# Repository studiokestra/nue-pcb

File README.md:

# Nue PCB rev1.1

This is the open source PCB for the Nue keyboard. It's minimally designed (as intentioned) with ISO support and basic 60% layout options. The Nue PCB has gasket mounting tabs and as such will not work on any other keyboard. Fuse / ESD protection was not implemented initially as this was taken care of by the unifed C3 daughterboard, however future revisions will have it onboard as backup. These files are provided as-is and are intended for tinkerers, do not expect warranty or support to be provided.

## Features
- Designed with KiCad 6.0+
- Compatible with QMK/VIA
- Only works with Nue PCB
- Utilizes Unified C3 daughterboard or compatible equivalents
- ISP header

## Supported layouts

## Ordering
The files necessary to produce the PCBs via JLCPCB are located in the production folder.

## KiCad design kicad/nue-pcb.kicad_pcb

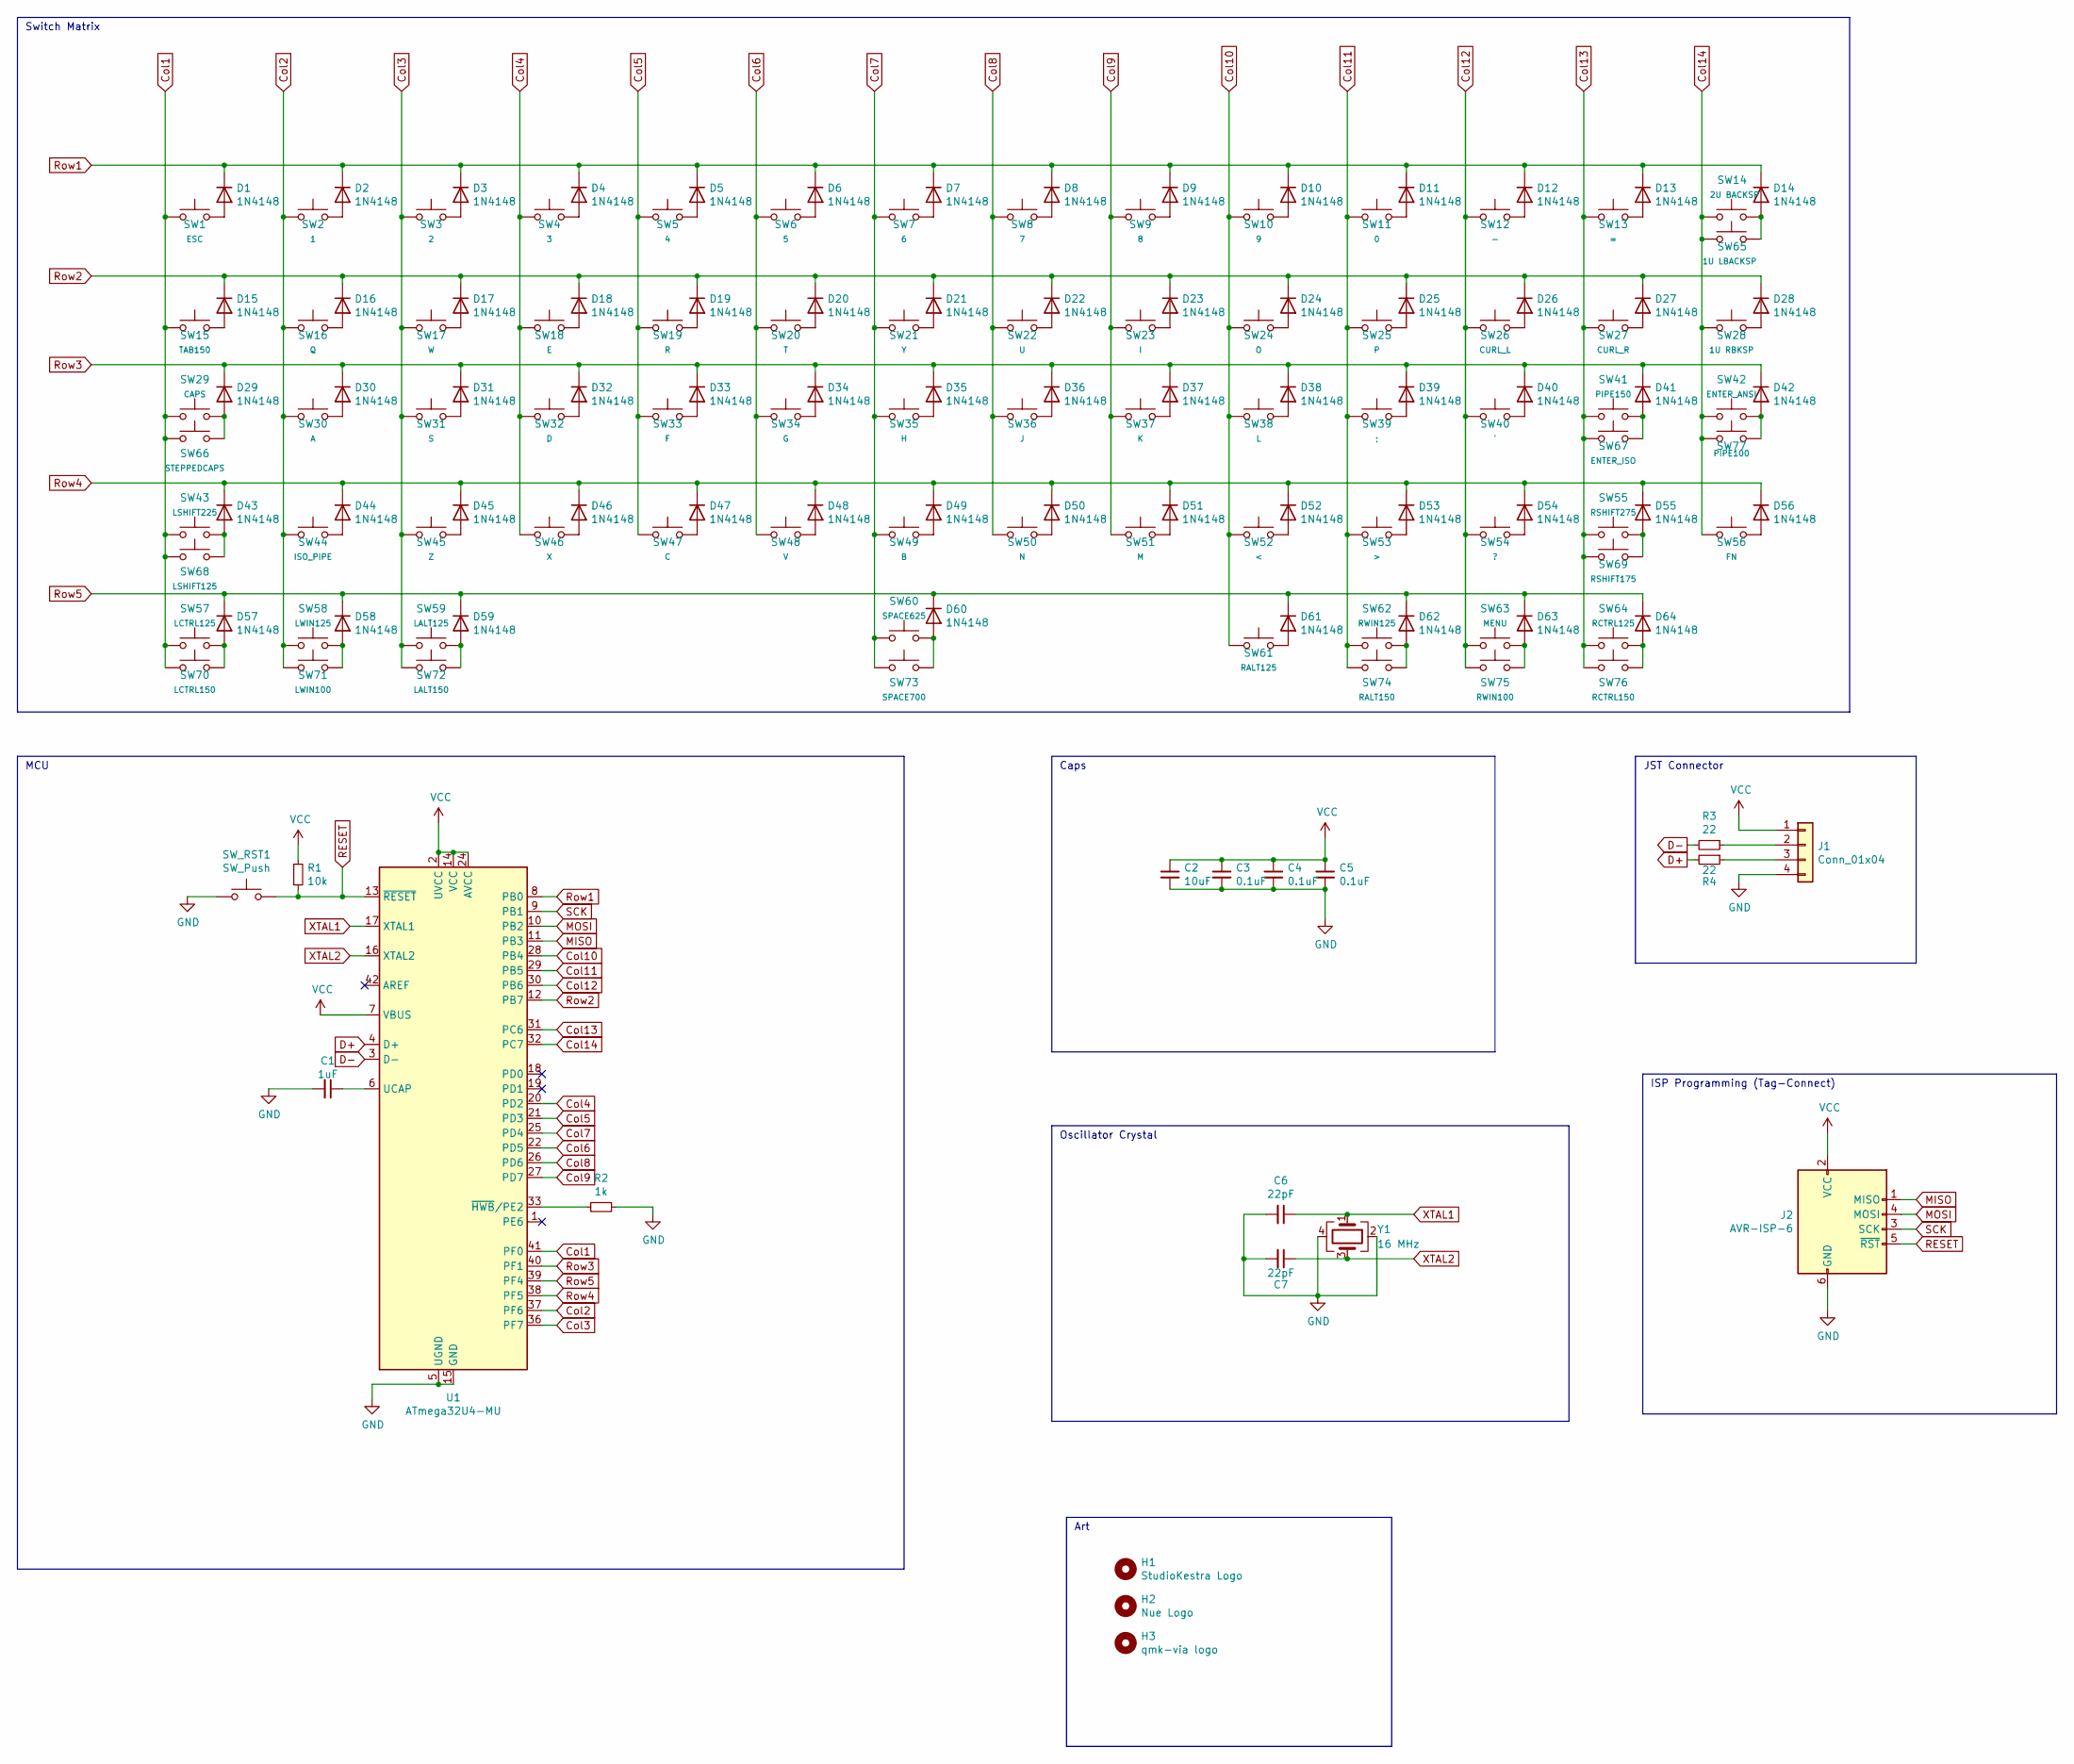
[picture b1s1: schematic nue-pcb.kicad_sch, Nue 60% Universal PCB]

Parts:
C1: 1uF; C_0603_1608Metric
C2: 10uF; C_0603_1608Metric
C3, C4, C5: 0.1uF; C_0603_1608Metric
C6, C7: 22pF; C_0603_1608Metric
D1, D2, D3, D4, D5, D6, D7, D8, D9, D10, D11, D12, D13, D14, D15, D16, D17, D18, D19, D20, D21, D22, D23, D24, D25, D26, D27, D28, D29, D30, D31, D32, D33, D34, D35, D36, D37, D38, D39, D40, D41, D42, D43, D44, D45, D46, D47, D48, D49, D50, D51, D52, D53, D54, D55, D56, D57, D58, D59, D60, D61, D62, D63, D64: 1N4148; D_SOD-123
H1: StudioKestra Logo; sk-square-mask-md
H2: Nue Logo; nue-logo
H3: qmk-via logo; qmk-via
J1: Conn_01x04; JST_BM04B-ASRS
J2: AVR-ISP-6; Conn_AVR_ISP_6
R1: 10k; R_0603_1608Metric
R2: 1k; R_0603_1608Metric
R3, R4: 22; R_0603_1608Metric
SW1: ESC; MX100
SW2: 1; MX100
SW3: 2; MX100
SW4: 3; MX100
SW5: 4; MX100
SW6: 5; MX100
SW7: 6; MX100
SW8: 7; MX100
SW9: 8; MX100
SW10: 9; MX100
SW11: 0; MX100
SW12: -; MX100
SW13: =; MX100
SW14: 2U BACKSP; MX200
SW15: TAB150; MX150
SW16: Q; MX100
SW17: W; MX100
SW18: E; MX100
SW19: R; MX100
SW20: T; MX100
SW21: Y; MX100
SW22: U; MX100
SW23: I; MX100
SW24: O; MX100
SW25: P; MX100
SW26: CURL_L; MX100
SW27: CURL_R; MX100
SW28: 1U RBKSP; MX100
SW29: CAPS; MX175
SW30: A; MX100
SW31: S; MX100
SW32: D; MX100
SW33: F; MX100
SW34: G; MX100
SW35: H; MX100
SW36: J; MX100
SW37: K; MX100
SW38: L; MX100
SW39: ;; MX100
SW40: '; MX100
SW41: PIPE150; MX150
SW42: ENTER_ANSI; MX225R
SW43: LSHIFT225; MX225
SW44: ISO_PIPE; MX100
SW45: Z; MX100
SW46: X; MX100
SW47: C; MX100
SW48: V; MX100
SW49: B; MX100
SW50: N; MX100
SW51: M; MX100
SW52: <; MX100
SW53: >; MX100
SW54: ?; MX100
SW55: RSHIFT275; MX275
SW56: FN; MX100
SW57: LCTRL125; MX125
SW58: LWIN125; MX125
SW59: LALT125; MX125
SW60: SPACE625; MX625R
SW61: RALT125; MX125
SW62: RWIN125; MX125
SW63: MENU; MX125
SW64: RCTRL125; MX125
SW65: 1U LBACKSP; MX100
SW66: STEPPEDCAPS; MX125
SW67: ENTER_ISO; MXISOEnter
SW68: LSHIFT125; MX125
SW69: RSHIFT175; MX175
SW70: LCTRL150; MX150
SW71: LWIN100; MX100
SW72: LALT150; MX150
SW73: SPACE700; MX700R
SW74: RALT150; MX150
SW75: RWIN100; MX100
SW76: RCTRL150; MX150
SW77: PIPE100; MX100
SW_RST1: SW_Push; pushbtn_C319436
U1: ATmega32U4-MU; QFN-44-1EP_7x7mm_P0.5mm_EP5.2x5.2mm
Y1: 16 MHz; Crystal_SMD_2520-4Pin_2.5x2.0mm

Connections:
Col1: SW1.1, SW15.1, SW29.1, SW43.1, SW57.1, SW66.1, SW68.1, SW70.1, U1.41 (PF0)
Col2: SW2.1, SW16.1, SW30.1, SW44.1, SW58.1, SW71.1, U1.37 (PF6)
Col3: SW3.1, SW17.1, SW31.1, SW45.1, SW59.1, SW72.1, U1.36 (PF7)
Col4: SW4.1, SW18.1, SW32.1, SW46.1, U1.20 (PD2)
Col5: SW5.1, SW19.1, SW33.1, SW47.1, U1.21 (PD3)
Col6: SW6.1, SW20.1, SW34.1, SW48.1, U1.22 (PD5)
Col7: SW7.1, SW21.1, SW35.1, SW49.1, SW60.1, SW73.1, U1.25 (PD4)
Col8: SW8.1, SW22.1, SW36.1, SW50.1, U1.26 (PD6)
Col9: SW9.1, SW23.1, SW37.1, SW51.1, U1.27 (PD7)
Col10: SW10.1, SW24.1, SW38.1, SW52.1, SW61.1, U1.28 (PB4)
Col11: SW11.1, SW25.1, SW39.1, SW53.1, SW62.1, SW74.1, U1.29 (PB5)
Col12: SW12.1, SW26.1, SW40.1, SW54.1, SW63.1, SW75.1, U1.30 (PB6)
Col13: SW13.1, SW27.1, SW41.1, SW55.1, SW64.1, SW67.1, SW69.1, SW76.1, U1.31 (PC6)
Col14: SW14.1, SW28.1, SW42.1, SW56.1, SW65.1, SW77.1, U1.32 (PC7)
D+: R4.2, U1.4 (D+)
D-: R3.2, U1.3 (D-)
GND: C1.2, C2.2, C3.2, C4.2, C5.2, C6.2, C7.2, J1.4, J2.6 (GND), R2.1, SW_RST1.1, U1.5 (UGND), U1.15 (GND), U1.23 (GND), U1.35 (GND), U1.43 (GND), U1.45 (GND), Y1.2, Y1.4
MISO: J2.1 (MISO), U1.11 (PB3)
MOSI: J2.4 (MOSI), U1.10 (PB2)
unnamed: C1.1, U1.6 (UCAP)
unnamed: D1.2 (A), SW1.2
unnamed: D2.2 (A), SW2.2
unnamed: D3.2 (A), SW3.2
unnamed: D4.2 (A), SW4.2
unnamed: D5.2 (A), SW5.2
unnamed: D6.2 (A), SW6.2
unnamed: D7.2 (A), SW7.2
unnamed: D8.2 (A), SW8.2
unnamed: D9.2 (A), SW9.2
unnamed: D10.2 (A), SW10.2
unnamed: D11.2 (A), SW11.2
unnamed: D12.2 (A), SW12.2
unnamed: D13.2 (A), SW13.2
unnamed: D14.2 (A), SW14.2, SW65.2
unnamed: D15.2 (A), SW15.2
unnamed: D16.2 (A), SW16.2
unnamed: D17.2 (A), SW17.2
unnamed: D18.2 (A), SW18.2
unnamed: D19.2 (A), SW19.2
unnamed: D20.2 (A), SW20.2
unnamed: D21.2 (A), SW21.2
unnamed: D22.2 (A), SW22.2
unnamed: D23.2 (A), SW23.2
unnamed: D24.2 (A), SW24.2
unnamed: D25.2 (A), SW25.2
unnamed: D26.2 (A), SW26.2
unnamed: D27.2 (A), SW27.2
unnamed: D28.2 (A), SW28.2
unnamed: D29.2 (A), SW29.2, SW66.2
unnamed: D30.2 (A), SW30.2
unnamed: D31.2 (A), SW31.2
unnamed: D32.2 (A), SW32.2
unnamed: D33.2 (A), SW33.2
unnamed: D34.2 (A), SW34.2
unnamed: D35.2 (A), SW35.2
unnamed: D36.2 (A), SW36.2
unnamed: D37.2 (A), SW37.2
unnamed: D38.2 (A), SW38.2
unnamed: D39.2 (A), SW39.2
unnamed: D40.2 (A), SW40.2
unnamed: D41.2 (A), SW41.2, SW67.2
unnamed: D42.2 (A), SW42.2, SW77.2
unnamed: D43.2 (A), SW43.2, SW68.2
unnamed: D44.2 (A), SW44.2
unnamed: D45.2 (A), SW45.2
unnamed: D46.2 (A), SW46.2
unnamed: D47.2 (A), SW47.2
unnamed: D48.2 (A), SW48.2
unnamed: D49.2 (A), SW49.2
unnamed: D50.2 (A), SW50.2
unnamed: D51.2 (A), SW51.2
unnamed: D52.2 (A), SW52.2
unnamed: D53.2 (A), SW53.2
unnamed: D54.2 (A), SW54.2
unnamed: D55.2 (A), SW55.2, SW69.2
unnamed: D56.2 (A), SW56.2
unnamed: D57.2 (A), SW57.2, SW70.2
unnamed: D58.2 (A), SW58.2, SW71.2
unnamed: D59.2 (A), SW59.2, SW72.2
unnamed: D60.2 (A), SW60.2, SW73.2
unnamed: D61.2 (A), SW61.2
unnamed: D62.2 (A), SW62.2, SW74.2
unnamed: D63.2 (A), SW63.2, SW75.2
unnamed: D64.2 (A), SW64.2, SW76.2
unnamed: J1.2, R3.1
unnamed: J1.3, R4.1
unnamed: R2.2, U1.33 (~HWB/PE2)
RESET: J2.5 (~RST), R1.2, SW_RST1.2, U1.13 (~RESET)
Row1: D1.1 (K), D2.1 (K), D3.1 (K), D4.1 (K), D5.1 (K), D6.1 (K), D7.1 (K), D8.1 (K), D9.1 (K), D10.1 (K), D11.1 (K), D12.1 (K), D13.1 (K), D14.1 (K), U1.8 (PB0)
Row2: D15.1 (K), D16.1 (K), D17.1 (K), D18.1 (K), D19.1 (K), D20.1 (K), D21.1 (K), D22.1 (K), D23.1 (K), D24.1 (K), D25.1 (K), D26.1 (K), D27.1 (K), D28.1 (K), U1.12 (PB7)
Row3: D29.1 (K), D30.1 (K), D31.1 (K), D32.1 (K), D33.1 (K), D34.1 (K), D35.1 (K), D36.1 (K), D37.1 (K), D38.1 (K), D39.1 (K), D40.1 (K), D41.1 (K), D42.1 (K), U1.40 (PF1)
Row4: D43.1 (K), D44.1 (K), D45.1 (K), D46.1 (K), D47.1 (K), D48.1 (K), D49.1 (K), D50.1 (K), D51.1 (K), D52.1 (K), D53.1 (K), D54.1 (K), D55.1 (K), D56.1 (K), U1.38 (PF5)
Row5: D57.1 (K), D58.1 (K), D59.1 (K), D60.1 (K), D61.1 (K), D62.1 (K), D63.1 (K), D64.1 (K), U1.39 (PF4)
SCK: J2.3 (SCK), U1.9 (PB1)
VCC: C2.1, C3.1, C4.1, C5.1, J1.1, J2.2 (VCC), R1.1, U1.2 (UVCC), U1.7 (VBUS), U1.14 (VCC), U1.24 (AVCC), U1.34 (VCC), U1.44 (AVCC)
XTAL1: C6.1, U1.17 (XTAL1), Y1.1
XTAL2: C7.1, U1.16 (XTAL2), Y1.3

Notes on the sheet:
Oscillator Crystal
MCU
ISP Programming (Tag-Connect)
JST Connector
Caps
Switch Matrix
Art

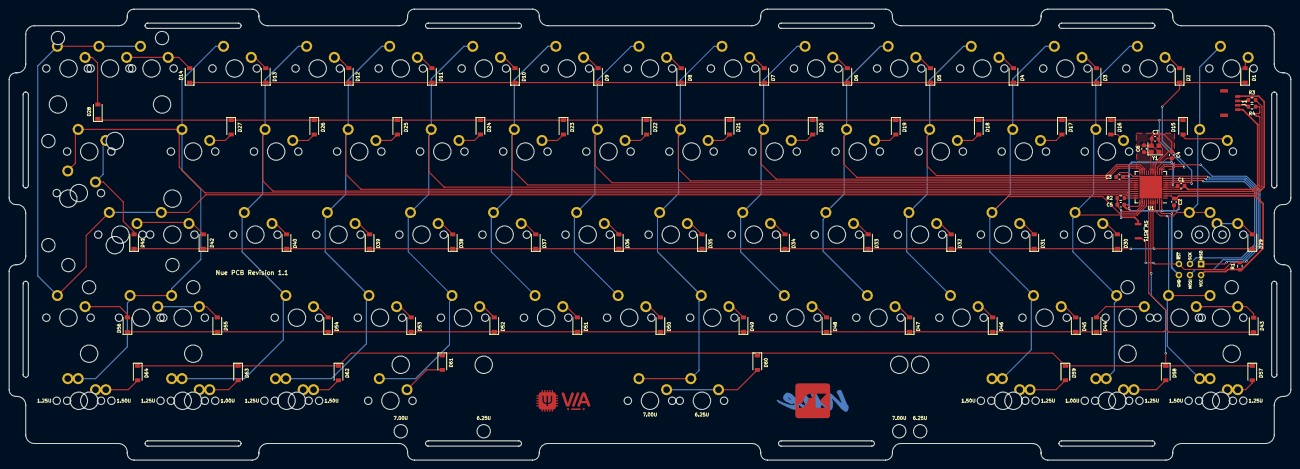
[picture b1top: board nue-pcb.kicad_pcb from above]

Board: 2 copper layers, 293.9 x 103.4 mm, 160 parts (1 on the bottom side), 97 nets.

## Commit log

2022-07-28 Initial commit.
2022-07-28 Update licensing.
2022-07-28 Updated the readme a bit.
